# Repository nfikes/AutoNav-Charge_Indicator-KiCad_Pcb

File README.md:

## AutoNav — Charge Indicator PCB

This repository contains the updated KiCad project for a compact, high-accuracy
battery charge-level indicator board. The design has evolved from a simple LED
threshold indicator into a more robust, instrumentation-grade battery monitor
using Texas Instruments (TI) power-management and monitoring ICs. The board is
intended to connect directly across the battery terminals (original target:
RBT245LFP pack) and provide a clear visual indication of pack state of charge.

## Images:

# Physical PCB:

# Routing:

# Schematic:

Overview
--------
The Charge Indicator PCB now uses TI analog front-end components, current-sense
amplifiers, and DC-DC regulation to deliver stable LED indicators across the
battery’s full operating voltage range. Measurement is performed using the
INA226 current/power monitor and processed with logic-level circuitry to drive
a bank of status LEDs corresponding to approximate SOC thresholds (100%, 80%,
60%, 40%, 20%, and critical/low).

Additional focus has been placed on noise immunity, transient protection, and
safe operation across the pack’s voltage extremes.

Key Features (Updated)
----------------------
- High-accuracy measurement using TI INA226 for voltage/current/power monitoring.
- Regulated low-voltage rail provided by TI TLV34063-based regulator (or similar
  TI DC/DC device).
- Configurable threshold indication using hardware logic and a 74HC164 shift
  register for stable LED control.
- Protection circuitry including input filtering, reverse-polarity protection,
  and transient suppression.
- Low-power design suitable for continuous monitoring with minimal impact on
  battery life.
- Compact SMT layout using 0603/0805/1210 components and custom Wavenumber
  footprints.
- Removable module mountable via Phoenix-style terminal connectors or solder pads.
- Easy BOM and fabrication generation directly inside KiCad.

Repository Structure
--------------------
- Charge_Indicator/Charge_Indicator.kicad_pro      — Full KiCad project.
- Charge_Indicator/Charge_Indicator.kicad_sch      — Updated schematic including
                                                     TI power monitor + regulation
                                                     circuitry.
- Charge_Indicator/Charge_Indicator.kicad_pcb      — PCB layout with revised
                                                     component placement and routing.
- Charge_Indicator-backups/                       — Automated KiCad backups.
- Battery Datasheets/                             — Datasheets for the RBT245LFP
                                                     battery pack.

Components of Interest
----------------------
Texas Instruments ICs included in the design:
- INA226 — Precision digital current/power/voltage monitor with I²C output.
- TLV34063-based regulator (or TLV34033/LM2596 variant) — Low-voltage regulation
  for logic and LED rail.
- BQ24120 (optional/regulating block depending on revision).
- 74HC164 — LED control/sequence logic, used to manage indicator states.

(If needed, replace these with the exact ICs used in the final version.)

Custom Footprints & Libraries
------------------------------
The project uses both standard KiCad libraries and Wavenumber footprint libraries.
These include:
- Resistors/capacitors (R0603, C1210, C0805, etc.)
- Phoenix-style connectors (e.g., wavenumber:1984617)
- Embedded STEP models for realistic 3D visualization

Quick Start — Opening & Editing the Project
-------------------------------------------
1. Launch KiCad and open:
   Charge_Indicator/Charge_Indicator.kicad_pro
2. From the project window, open Eeschema to view/edit the TI measurement and
   regulation circuitry.
3. Open pcbnew to inspect component placement, routing, and copper pours.
4. To generate a BOM:
   Eeschema → Tools → Generate Bill of Materials
5. To generate fabrication outputs:
   pcbnew → File → Plot (Gerbers)
           → Fabrication Outputs → Drill Files

KiCad Version Compatibility
---------------------------
The project was created using KiCad 8/9 toolchain (schema version 9.0, updated
2025-01-14). It is recommended to use KiCad 7 or newer.

If you experience compatibility issues, please open an issue with details about
your KiCad version and the error message.

Contact / Author
- Repository owner: `nfikes` (GitHub).
- Repository collaborator: `ehughes` (GitHub).

PCB Assembly & Bring-Up Procedure
---------------------------------

Follow this procedure when building a new board.

**Rev 4+ voltage divider change:** The external voltage divider was changed
from R27 = 200 kΩ / R22 = 34.8 kΩ (ratio 6.75) to R27 = 200 kΩ /
R22 = 6.49 kΩ (ratio 31.82). This keeps the BAT pin below 1 V at maximum
pack voltage (30 V), making the BQ34Z100-R2 ADC safe **regardless of
VOLTSEL state**. The factory default VOLTSEL = 1 is now the correct setting.

### Step 1 — Solder all components

Populate all components on the board, including the BQ34Z100-R2 (U1).
With the new voltage divider, no special precautions are needed for U1.

### Step 2 — Continuity test (unpowered)

With the board **unpowered**, perform a continuity test on the load and power
terminals. Verify there are no shorts or unintended connections.

### Step 3 — Initial power-on test

Apply **10 V** to the power input and place a **1 MΩ resistor** across the
load terminal.

### Step 4 — Verify 5 V rail

Measure the **5 V pad** with a multimeter. If it reads 5 V, install the
solder bridge to connect the 5 V rail.

### Step 5 — Verify 3.3 V rail

Measure the **3.3 V pad** with a multimeter. If it reads 3.3 V, install the
solder bridge to connect the 3.3 V rail.

### Step 6 — Verify voltage divider / OP-AMP output

Measure the output of the OP-AMP that connects to the BAT pin:

- **Divider OFF (MOSFET array disabled):** should read negative millivolts
  (~0 V).
- **Divider ON (MOSFET array enabled):** should read the divided 10 V input
  (approximately 10 V / 31.82 ≈ 0.314 V).

### Step 7 — Communication tests

Connect the Aardvark I2C adapter and run both communication tests:

```
cd Programming/scripts
python3 ina226_comm_test.py
python3 bq_comm_test.py
```

`bq_comm_test.py` will verify that VOLTSEL = 1 (correct for the new divider)
and that RSNS is set correctly for low-side sensing.

### Step 8 — Enable the voltage divider

Turn on the MOSFET array to connect the voltage divider to the BAT pin.
With the new divider, the BAT pin will see ≤ 1 V regardless of VOLTSEL
state — both VOLTSEL = 0 and VOLTSEL = 1 are safe.

Initial Board Programming (BQ34Z100-R2)
----------------------------------------

After completing the assembly and bring-up procedure above, the BQ34Z100-R2
must be programmed with battery parameters before the board will report
accurate voltage, SOC, or current. All configuration is stored in
non-volatile Data Flash and persists across power cycles.

### Hardware required

- Total Phase Aardvark I2C adapter (connected to the board's I2C header)
- 24 V power supply or the Renogy RBT2425LFP battery pack

### Voltage divider and VOLTSEL

The BQ34Z100-R2 has an internal 5:1 voltage divider on the BAT pin. The
board's external resistor divider (R27 = 200 kΩ / R22 = 6.49 kΩ) steps the
~25.6 V pack voltage down to ~0.8 V at the BAT pin — safely below the ADC's
1 V limit in **both** VOLTSEL modes:

- **VOLTSEL = 1** (factory default, internal divider bypassed): ADC sees the
  BAT pin voltage directly (~0.8 V). Best ADC resolution.
- **VOLTSEL = 0** (internal 5:1 divider active): ADC sees BAT / 5 (~0.16 V).
  Still safe, but lower resolution.

VOLTSEL = 1 is the **correct and preferred** setting for this board.

> **Historical note (Rev 2–3):** Earlier revisions used R22 = 34.8 kΩ, which
> put ~3.8 V on the BAT pin. With VOLTSEL = 1 (factory default), the full
> 3.8 V reached the ADC, permanently destroying the analog front end. Three
> chips were damaged this way. The Rev 4+ divider eliminates this failure
> mode entirely.

### Programming procedure

1. **Connect the Aardvark** to the board's I2C header with target power
   enabled.
2. **Run communication tests**:
   ```
   cd Programming/scripts
   python3 ina226_comm_test.py
   python3 bq_comm_test.py
   ```
3. **Enable the MOSFET array** if not already on.
4. **Run board diagnostics** to confirm I2C communication with both the
   INA226 and BQ34Z100-R2:
   ```
   python3 pcb_diagnostics.py
   ```
5. **Program battery parameters** (cell count, capacity, voltage divider
   ratio, QMax):
   ```
   python3 bq_program_battery.py
   ```
6. **Program the LiFePO4 chemistry profile** (R_a resistance tables, design
   parameters, voltage calibration using the INA226 as ground truth):
   ```
   python3 bq_program_chemistry.py
   ```
7. **Verify final readings** — re-run diagnostics and confirm that
   `Voltage()`, SOC, and temperature are reporting sensible values:
   ```
   python3 pcb_diagnostics.py
   ```

### After programming

- The chip seals itself automatically after each flash commit. Normal
  operation does not require the device to be unsealed.
- Configuration survives power cycles indefinitely — no reprogramming is
  needed unless you want to change parameters.
- If voltage reads 0 mV after programming, run `bq_fix_vdivider.py` to
  recalibrate the voltage divider using the INA226 as a reference.

### Programming scripts reference

All scripts are located in `Programming/scripts/`.

| Script                    | Purpose                                          |
|---------------------------|--------------------------------------------------|
| `ina226_comm_test.py`    | INA226 communication check (MFG/Die ID + regs)  |
| `bq_comm_test.py`        | BQ34Z100-R2 comm check + config verification     |
| `i2c_scan.py`            | Full I2C bus scan (all addresses 0x03-0x77)      |
| `bq_clear_voltsel.py`    | Standalone VOLTSEL tool (legacy, Rev 2-3 only)   |
| `pcb_diagnostics.py`     | Full I2C diagnostics for INA226 + BQ34Z100-R2    |
| `bq_program_battery.py`  | Write design capacity, cell count, VD, QMax      |
| `bq_program_chemistry.py`| LiFePO4 R_a tables + voltage calibration         |
| `bq_fix_vdivider.py`     | Recalibrate voltage divider via INA226            |
| `bq_calibrate.py`        | CC Gain / CC Delta calibration                   |
| `bq_debug_voltage.py`    | Dump all registers for voltage debugging         |
| `bq_full_reset.py`       | Factory reset the gauge                          |
| `ina226_monitor.py`      | Real-time GUI monitor (voltage/current/power)    |

Revision 2 Board Failure Report (Bowser → Shogi Transfer)
----------------------------------------------------------

**Date:** 2026-04-23
**Board:** Revision 2, serial originally deployed on robot Bowser
**Status:** Declared dead

### Background

The R2 board was transferred from robot Bowser to robot Shogi. It was
fully functional on Bowser. After installation on Shogi, I2C
communication failed completely.

### Suspected Root Cause

Metal shavings from the robot chassis are suspected to have landed on
the board, creating transient shorts across exposed traces and
component pads. This triggered cascading failures in multiple ICs.

### Failure 1 — INA226 (U3) CMOS Latch-Up

**Symptom:** SCL held at ~3 ohms to ground. No I2C devices responded.

**Diagnosis:** With U3 removed, SCL-to-GND resistance rose from 3 ohms
to 200 kohms. Using the parallel resistance formula:

    1/R_total = 1/R_ina + 1/R_board
    R_ina ≈ 5.0 ohms

The INA226 had a ~5 ohm internal short from SCL to ground — consistent
with CMOS latch-up, where a parasitic PNPN thyristor (SCR) structure
activates and creates a self-sustaining low-impedance path. A metal
shaving shorting an I/O pin above or below the supply rails would
forward-bias the internal ESD protection diodes, injecting substrate
current and triggering the parasitic SCR.

**Resolution:** Replaced U3 (INA226). SCL impedance restored to normal.

### Failure 2 — SGM61410 (U2) DC-DC Buck Converter

**Symptom:** 5 V buck output only produced ~1.15 V from a 20 V input.
The downstream 3.3 V LDO (U5, TPS7A2033) also showed only ~1 V output.

**Diagnosis:**
- U2 pin 5 (VIN): 19.99 V — input is fine
- U2 pin 6 (SW): 1.15 V — not switching properly
- U2 pin 3 (FB): 1.144 V — essentially equal to the output

The feedback pin reading the full output voltage indicates the feedback
divider network is broken. The bottom resistor (FB to GND) is likely
open, causing FB to float to the output voltage through the top
resistor. The converter sees FB above its 0.6 V reference and
throttles switching to minimum duty cycle.

**Resolution:** None — board declared dead. The feedback network damage
combined with potential internal U2 damage makes further rework
impractical.

### Lessons Learned

1. Metal shavings from robot chassis work can cause catastrophic
   multi-IC failures through transient shorts and CMOS latch-up.
2. The INA226 SCL pin is particularly vulnerable — its absolute maximum
   is only VS + 0.3 V, and the 5.6 V zener ESD clamps (D8/D9) on this
   board clamp above that threshold.
3. **All future PCBs mandate a protective housing.** Bare boards must
   not be deployed on robots without an enclosure to prevent metallic
   debris from reaching exposed components and traces.
4. When one IC fails from an external short event, inspect all ICs on
   the board — cascading damage is likely.

Battery Datasheets
------------------
Reference documentation for the RBT2425LFP LiFePO4 battery:

https://github.com/nfikes/AutoNav-Charge_Indicator-KiCad_Pcb/blob/80e677aa5d561c7ffa7e2566f1dbaed0d212a4c6/Battery%20Datasheets/RBT2425LFP%20-%20Datasheet.pdf

https://github.com/nfikes/AutoNav-Charge_Indicator-KiCad_Pcb/blob/80e677aa5d561c7ffa7e2566f1dbaed0d212a4c6/Battery%20Datasheets/RBT2425LFP%20-%20User%20Manual.pdf

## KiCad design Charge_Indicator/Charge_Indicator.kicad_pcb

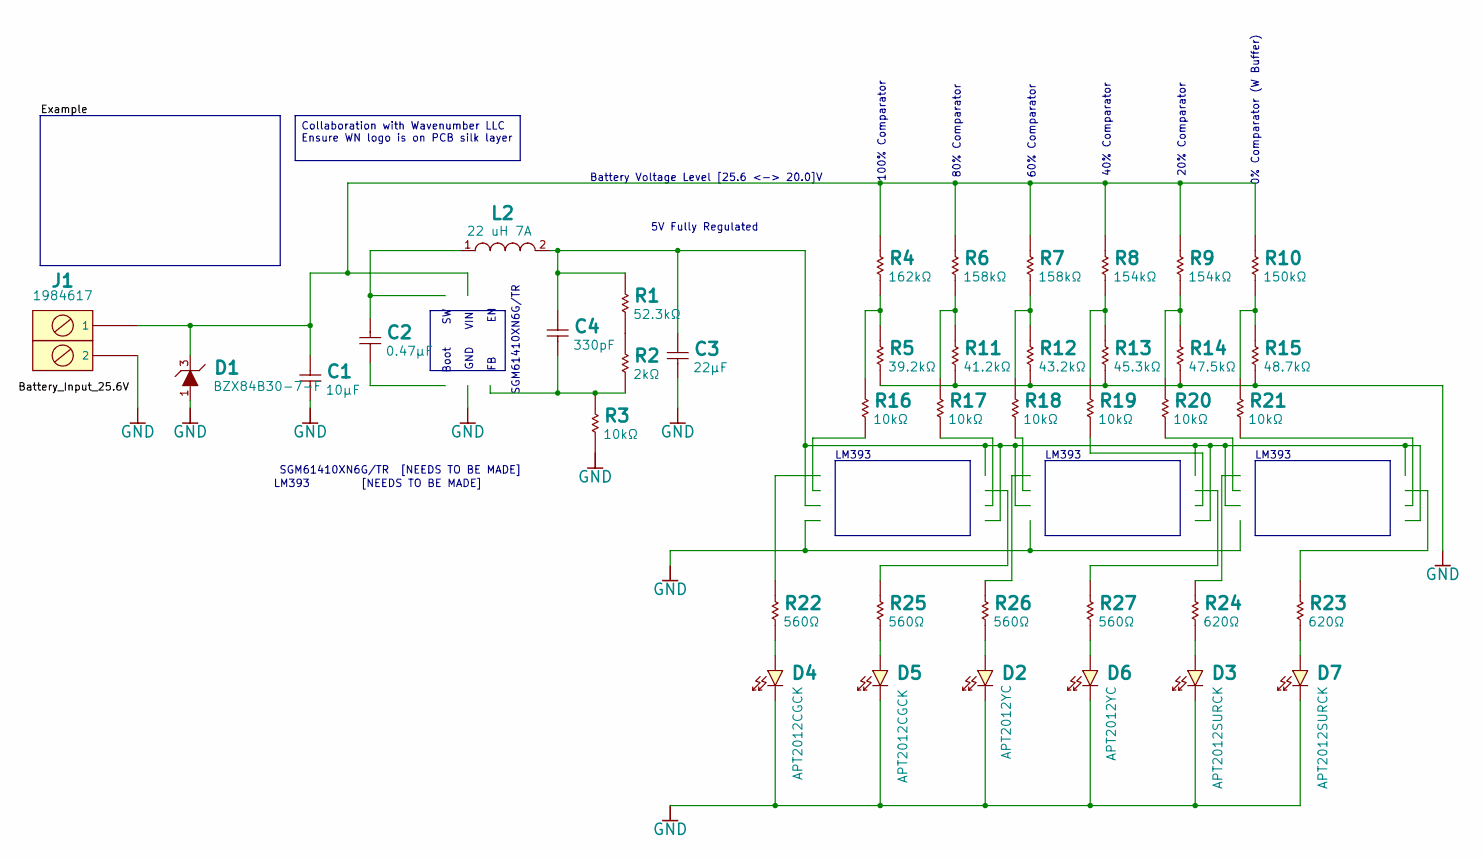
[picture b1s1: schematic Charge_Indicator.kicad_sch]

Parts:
C1: 10µF; C1210_2.70MM_MD; Manufacturer Part Number GCM32EC71H106KA03K
C2: 0.47µF; C0805_1.45MM_MD; Manufacturer Part Number GCJ21BR71H474KA12L
C3: 22µF; C1210_2.80MM_MD; Manufacturer Part Number GCJ32ER71C226KE01L
C4: 330pF; C0805_1.00MM_MD; Manufacturer Part Number GCM21A7U2E331JX01D
D1: BZX84B30-7-F; D_SOT-23-3_P; Manufacturer Part Number BZX84B30-7-F
D2, D6: APT2012YC; LED-0805-YELLOW; Manufacturer Part Number APT2012YCdef
D3, D7: APT2012SURCK; LED-0805-RED; Manufacturer Part Number APT2012SURCK
D4, D5: APT2012CGCK; LED-0805-GREEN; Manufacturer Part Number APT2012CGCK
J1: 1984617; Manufacturer Part Number 1984617
L2: 22 uH 7A; L_DO5010H_800; Manufacturer Part Number DO5010H-223ML
R1: 52.3kΩ; R0603_0.55MM_HD; Manufacturer Part Number ERJ-3EKF5232V
R2: 2kΩ; R0603_0.55MM_HD; Manufacturer Part Number ERJ-3EKF2001V
R3, R16, R17, R18, R19, R20, R21: 10kΩ; R0603_0.55MM_HD; Manufacturer Part Number ERJ-3EKF1002V
R4: 162kΩ; R0603_0.55MM_HD; Manufacturer Part Number ERJ-3EKF1623V
R5: 39.2kΩ; R0603_0.55MM_HD; Manufacturer Part Number ERJ-3EKF3922V
R6, R7: 158kΩ; R0603_0.55MM_HD; Manufacturer Part Number ERJ-3EKF1583V
R8, R9: 154kΩ; R0603_0.55MM_HD; Manufacturer Part Number ERJ-3EKF1543V
R10: 150kΩ; R0603_0.55MM_HD; Manufacturer Part Number ERJ-3EKF1503V
R11: 41.2kΩ; R0603_0.55MM_HD; Manufacturer Part Number ERJ-3EKF4122V
R12: 43.2kΩ; R0603_0.55MM_HD; Manufacturer Part Number ERJ-3EKF4322V
R13: 45.3kΩ; R0603_0.55MM_HD; Manufacturer Part Number ERJ-3EKF4532V
R14: 47.5kΩ; R0603_0.55MM_HD; Manufacturer Part Number ERJ-3EKF4752V
R15: 48.7kΩ; R0603_0.55MM_HD; Manufacturer Part Number ERJ-3EKF4872V
R22, R25, R26, R27: 560Ω; R0603_0.55MM_HD; Manufacturer Part Number ERJ-3EKF5600V
R23, R24: 620Ω; R0603_0.55MM_HD; Manufacturer Part Number ERJ-3EKF6200V

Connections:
GND: C1.2 (1), C3.2 (1), D1.1 (A), D2.C, D3.C, D4.C, D5.C, D6.C, D7.C, J1.2, R3.2, R5.2, R11.2, R12.2, R13.2, R14.2, R15.2
unnamed: C2.2 (1), L2.1
unnamed: C3.1, C4.1, L2.2, R1.1
unnamed: C4.2 (1), R2.2, R3.1
unnamed: C1.1, D1.3 (K), J1.1, R4.1, R6.1, R7.1, R8.1, R9.1, R10.1
unnamed: D2.A, R26.1
unnamed: D3.A, R24.1
unnamed: D4.A, R22.1
unnamed: D5.A, R25.1
unnamed: D6.A, R27.1
unnamed: D7.A, R23.1
unnamed: R1.2, R2.1
unnamed: R10.2, R15.1, R21.1
unnamed: R6.2, R11.1, R17.1
unnamed: R7.2, R12.1, R18.1
unnamed: R8.2, R13.1, R19.1
unnamed: R9.2, R14.1, R20.1
unnamed: R4.2, R5.1, R16.1

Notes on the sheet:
60% Comparator
SGM61410XN6G/TR
LM393
LM393 [NEEDS TO BE MADE]
GND VIN
SGM61410XN6G/TR [NEEDS TO BE MADE]
40% Comparator
0% Comparator (W Buffer)
Battery Voltage Level [25.6 <-> 20.0]V
100% Comparator
20% Comparator
5V Fully Regulated
Boot SW
FB EN
80% Comparator
Collaboration with Wavenumber LLC Ensure WN logo is on PCB silk layer

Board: 2 copper layers, 40 parts (0 on the bottom side), 18 nets, no tracks yet.

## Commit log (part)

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2025-11-04 Charge Indicator Board Schematic Layout Preliminary
    Adding KiCad PCB project with schematic for working circuit of a Battery Level indicator specifically designed for the RBT2425LFP Battery.
2025-11-04 Add battery level indication PCB details to README
    Added details about the battery level indication PCB, including its purpose and desired functionality.
2025-11-04 Adding some more text to the schematic
2025-11-04 Updating the README
2025-11-04 Adding pull ups, reversing logic, adding simulation validation image
2025-11-05 Adding KiCad generated symbols for SMT components
    Summary of changes:
    - Adding in the kicad_mod and kicad_sym of each of the components.
    - (might be errors with how these libraries are linked up from the local dir)
    - Fixed a wrong resistor in the schematic.
    - Moved around graphics.
2025-11-05 Adding the Datasheets for the battery
    Useful for determining the load at the PCB terminals.
2025-11-05 Updating the README to include the datasheet links.
2025-11-07 Using TI chips for power detection putting everything together.
2025-11-11 Adding Zero Ohms and Test Points on 5 and 3.3 points
    Summary of Changes:
    - On the buck output is a test point and zero ohm to ensure there is 5V constant.
    - On the regulator output is a test point and zero ohm to ensure there is 3.3V constant.
2025-11-11 Many changes to the PCB schematic and PCB layout.
    Summary of changes:
    - Using new added chips to wn_pcb branch to connect up into KiCad automatically.
    - Added another PZ254-2-02-S Dupont connection port for the 3v3 line, Alert pin, and HDQ highspeed data acquisition pin.
    - Cleaned up the schematic a bit to make it less confusing.
    - Added 0 Ohm resistors in front of both the buck and regulator so that 3v3 and 5v0 can be checked before real testing.
    - EN pin of the SGM61410XN6G_TR is tied to VIN like stated in the datasheet.
2025-11-11 Revise README for Charge Indicator PCB enhancements
    Updated the README to reflect enhancements in the Charge Indicator PCB design, including improved accuracy and additional features.
2025-11-11 added project specfic fp library as example
2025-11-13 Linking up local libraries
    Linking up the symbols and footprints using local libraries for this project.
2025-11-14 WIP routing
2025-11-15 Finished routing, might need some changes
2025-11-22 SW1 Wiring - fix
    Summary of Changes:
    - Pin 2 of the switch is now connected to R17.
    - M on the switch is now on Ground.
    - Re-routed on PCB side, now ground polygons span entire PCB to encompass switch grounds.
2025-11-22 Global Label vs Power Symbol vs NetLabel fix
    Summary of Changes:
    - Global labels are now Net Labels.
    - Power rails now have their own power symbol.
2025-11-22 Move output caps fix
    Summary of Changes:
    - 5v0 and 3v3 lines now have their decoupling capacitors next to the test points before the 0 Ohm resistors.
    - Reroute to carry the change to the PCB.
2025-11-22 Sch Style / Intent fix
    Summary of Changes:
    - Major overhaul to how the Schematic side is presented. Now the Sch side is in blocks.
    - Some symbols were updated to create more space and ease of viewing.
    - New lower side current sense resistor at 0.005 Ohms at 2.5 W.
    - New PCB silkscreen Layer items.
2025-11-22 Fix small little trace visual inconsistency on C5.
2025-11-24 Fixing errors in the PCB related to the DRC
2025-11-24 Switching around the Silkscreen layer text
2025-11-24 swapped U5 for SOT23-5 variant
2025-11-24 Using new package size for the regulator and getting PCB ready
2025-11-29 Including a couple raw BOM sheets.
2025-11-29 Including Order Sheet.
2025-11-29 Add images to README for PCB and schematic
    Added images of the PCB, routing, and schematic.
2025-11-29 Update README with images section
    Added images section with physical PCB, routing, and schematic.
2025-12-01 Updating the order sheet to include real costs.
2025-12-28 Slight changes to schematic
2025-12-29 Making changes
2025-12-30 Changed silklayer text
2026-01-05 DRC checks and finishing touches
2026-01-15 Changes and Exporting fab files
2026-02-03 Invoices and Budget tracking documents
2026-02-03 Adjust invoices
2026-02-06 Aardvark I2C quick diagnostics
2026-02-10 Some updates to the diagnostics program and the order sheet.
2026-02-18 Organizing.
2026-02-19 Changes to the PCB for REV 3
2026-02-19 More up to date images
2026-02-19 Fabrication files for REV3
2026-02-19 Fixing Net issue
2026-03-20 Changing direction to modifying the divider network.
2026-03-20 Swapping out resistors at the divider to protect the BQ chip
2026-03-20 Including drop in components for Rev3
2026-03-20 Fixing script issues.
2026-03-31 Updated order sheets
2026-04-01 BQ debugging and INA226 temp solution for coulomb counting
2026-04-01 Documentation
2026-04-01 More documentation for past endeavors
2026-04-01 More documentation of the distant past about early revisions
2026-04-03 SOC graph collecting
2026-04-04 Finishin up discharge data capture for coulomb counting
2026-04-05 Formatting for a report
2026-04-27 New research, updates to the GUI systems etc.
2026-04-28 New monitor to get the SOC charge left time.
2026-04-28 Was not using the right SOC method.
2026-05-08 Testing new custom init behavior.
2026-05-14 Updated files
2026-05-24 Giving the Wireless E-Stop schematic a home for now.
2026-05-24 Moving wireless E-Stop stuff to the base folder.
2026-05-25 Starting the SBUS Inverter schematic.
2026-05-25 Finishing up the SBUS inverter.
2026-05-25 Improving the circuit.
2026-06-03 Updated things.
2026-06-03 Add hardware recommendations for next team
    Add MESSAGE_FOR_NEXT_TEAM.md documenting hardware lessons from the 2025–2026 season. The file lists actionable recommendations for the Charge Indicator PCB: DIP switches for I²C addressing, a 10 A st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
2026-06-08 Bunch of stuff that I forgot to put up.
2026-06-21 Ignore KiCad fp-info-cache; untrack the committed copy
